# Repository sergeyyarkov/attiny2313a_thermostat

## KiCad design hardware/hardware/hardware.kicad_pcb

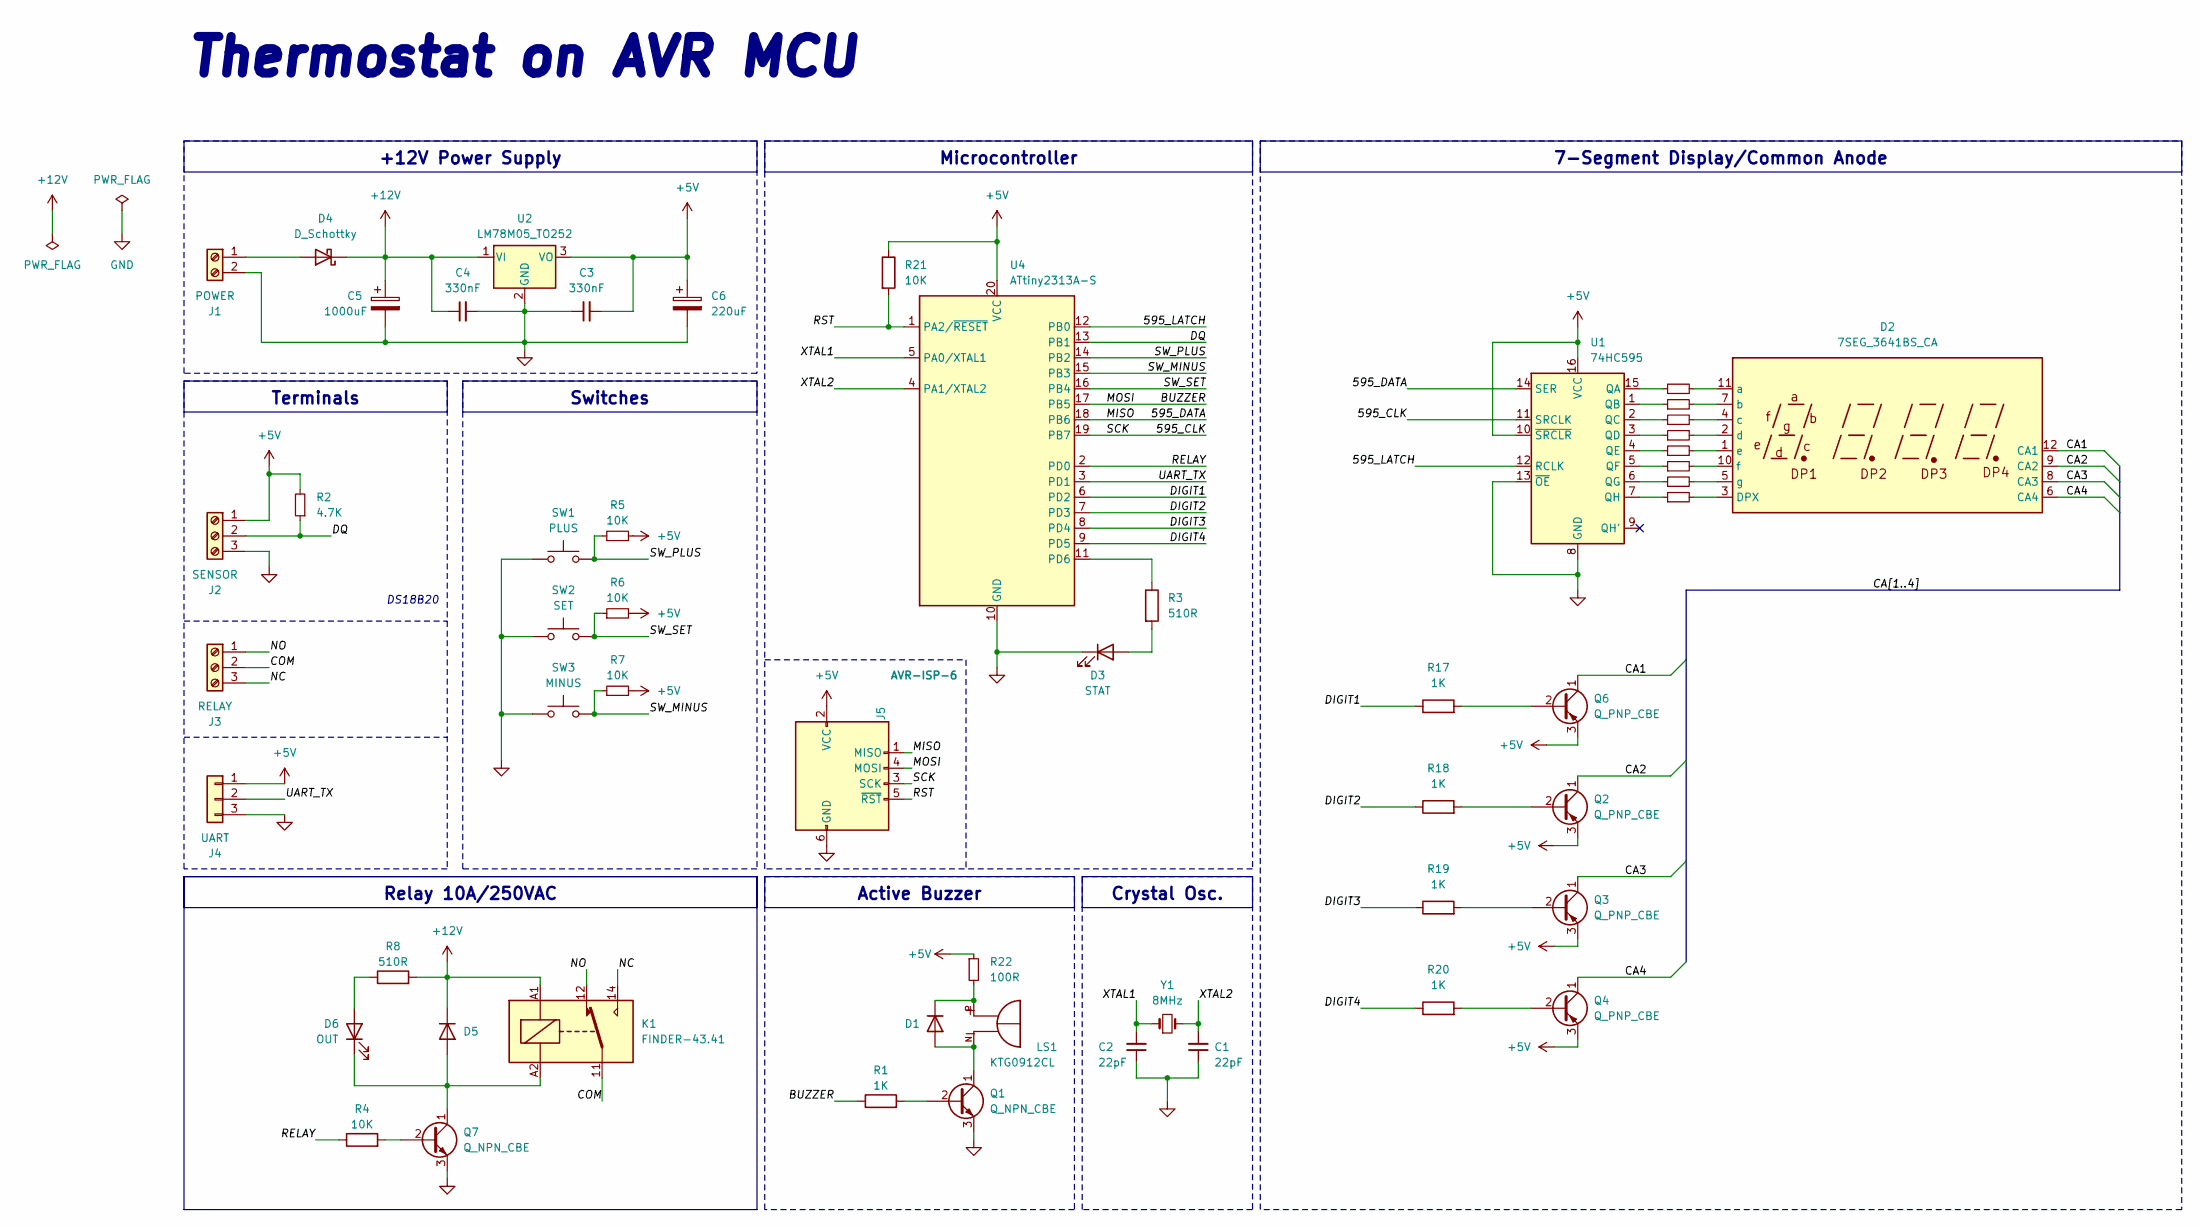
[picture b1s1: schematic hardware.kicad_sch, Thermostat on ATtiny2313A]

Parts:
C1, C2: 22pF; C_0805_2012Metric
C3, C4: 330nF; C_0805_2012Metric
C5: 1000uF; CP_Elec_10x10.5
C6: 220uF; CP_Elec_6.3x7.7
D1: 1N4448W; D_SOD-123
D2: 7SEG_3641BS_CA; 7SEG_3641BS
D3: STAT; LED_0805_2012Metric
D4: D_Schottky; D_SMA
D5: D; D_SMA
D6: OUT; LED_0805_2012Metric
J1: POWER; TerminalBlock_Phoenix_MPT-0,5-2-2.54_1x02_P2.54mm_Horizontal
J2: SENSOR; TerminalBlock_Phoenix_MPT-0,5-3-2.54_1x03_P2.54mm_Horizontal
J3: RELAY; TerminalBlock_Phoenix_MPT-0,5-3-2.54_1x03_P2.54mm_Horizontal
J4: UART; PinHeader_1x03_P2.54mm_Vertical
J5: AVR-ISP-6; PinHeader_2x03_P2.54mm_Vertical
K1: FINDER-43.41; RELAY_FINDER-43.41
LS1: KTG0912CL; XDCR_KTG0912CL; PARTREV 1.1
Q1, Q7: Q_NPN_CBE; SOT-23
Q2, Q3, Q4, Q6: Q_PNP_CBE; SOT-23
R1, R17, R18, R19, R20: 1K; R_0805_2012Metric
R2: 4.7K; R_0805_2012Metric
R3, R8: 510R; R_0805_2012Metric
R4, R5, R6, R7, R21: 10K; R_0805_2012Metric
R9, R10, R11, R12, R13, R14, R15, R16: 330R; R_0805_2012Metric
R22: 100R; R_0805_2012Metric
SW1: PLUS; SW_Push_1P1T_NO_6x6mm_H9.5mm
SW2: SET; SW_Push_1P1T_NO_6x6mm_H9.5mm
SW3: MINUS; SW_Push_1P1T_NO_6x6mm_H9.5mm
U1: 74HC595; SOIC-16W_5.3x10.2mm_P1.27mm
U2: LM78M05_TO252; TO-252-2
U4: ATtiny2313A-S; SOIC-20W_7.5x12.8mm_P1.27mm
Y1: 8MHz; Crystal_HC49-4H_Vertical

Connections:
+5V: C3.2, C6.1, J2.1, J4.1, J5.2 (VCC), Q2.3 (E), Q3.3 (E), Q4.3 (E), Q6.3 (E), R2.2, R5.2, R6.2, R7.2, R21.1, R22.1, U1.10 (~SRCLR), U1.16 (VCC), U2.3 (VO), U4.20 (VCC)
+12V: C4.1, C5.1, D4.1 (K), D5.1 (K), K1.A1, R8.2, U2.1 (VI)
/595_CLK: J5.3 (SCK), U1.11 (SRCLK), U4.19 (PB7)
/595_DATA: J5.1 (MISO), U1.14 (SER), U4.18 (PB6)
/595_LATCH: U1.12 (RCLK), U4.12 (PB0)
/BUZZER: J5.4 (MOSI), R1.1, U4.17 (PB5)
/CA1: D2.12 (CA1), Q6.1 (C)
/CA2: D2.9 (CA2), Q2.1 (C)
/CA3: D2.8 (CA3), Q3.1 (C)
/CA4: D2.6 (CA4), Q4.1 (C)
/COM: J3.2, K1.11
/DIGIT1: R17.1, U4.6 (PD2)
/DIGIT2: R18.1, U4.7 (PD3)
/DIGIT3: R19.1, U4.8 (PD4)
/DIGIT4: R20.1, U4.9 (PD5)
/DQ: J2.2, R2.1, U4.13 (PB1)
/NC: J3.3, K1.14
/NO: J3.1, K1.12
/RELAY: R4.1, U4.2 (PD0)
/RST: J5.5 (~RST), R21.2, U4.1 (PA2/~RESET)
/SW_MINUS: R7.1, SW3.2, U4.15 (PB3)
/SW_PLUS: R5.1, SW1.2, U4.14 (PB2)
/SW_SET: R6.1, SW2.2, U4.16 (PB4)
/UART_TX: J4.2, U4.3 (PD1)
/XTAL1: C2.2, U4.5 (PA0/XTAL1), Y1.1
/XTAL2: C1.2, U4.4 (PA1/XTAL2), Y1.2
GND: C1.1, C2.1, C3.1, C4.2, C5.2, C6.2, D3.1 (K), J1.2, J2.3, J4.3, J5.6 (GND), Q1.3 (E), Q7.3 (E), SW1.1, SW2.1, SW3.1, U1.8 (GND), U1.13 (~OE), U2.2 (GND), U4.10 (GND)
unnamed: D1.2 (A), LS1.N, Q1.1 (C)
unnamed: D1.1 (K), LS1.P, R22.2
unnamed: D2.3 (DPX), R16.2
unnamed: D2.11 (a), R9.2
unnamed: D2.7 (b), R10.2
unnamed: D2.4 (c), R11.2
unnamed: D2.2 (d), R12.2
unnamed: D2.1 (e), R13.2
unnamed: D2.10 (f), R14.2
unnamed: D2.5 (g), R15.2
unnamed: D3.2 (A), R3.2
unnamed: D4.2 (A), J1.1
unnamed: D5.2 (A), D6.1 (K), K1.A2, Q7.1 (C)
unnamed: D6.2 (A), R8.1
unnamed: Q1.2 (B), R1.2
unnamed: Q2.2 (B), R18.2
unnamed: Q3.2 (B), R19.2
unnamed: Q4.2 (B), R20.2
unnamed: Q6.2 (B), R17.2
unnamed: Q7.2 (B), R4.2
unnamed: R9.1, U1.15 (QA)
unnamed: R10.1, U1.1 (QB)
unnamed: R11.1, U1.2 (QC)
unnamed: R12.1, U1.3 (QD)
unnamed: R13.1, U1.4 (QE)
unnamed: R14.1, U1.5 (QF)
unnamed: R15.1, U1.6 (QG)
unnamed: R16.1, U1.7 (QH)
unnamed: R3.1, U4.11 (PD6)

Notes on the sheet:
Active Buzzer
Terminals
+12V Power Supply
Crystal Osc.
Relay 10A/250VAC
Switches
7-Segment Display/Common Anode
Microcontroller
Thermostat on AVR MCU
DS18B20

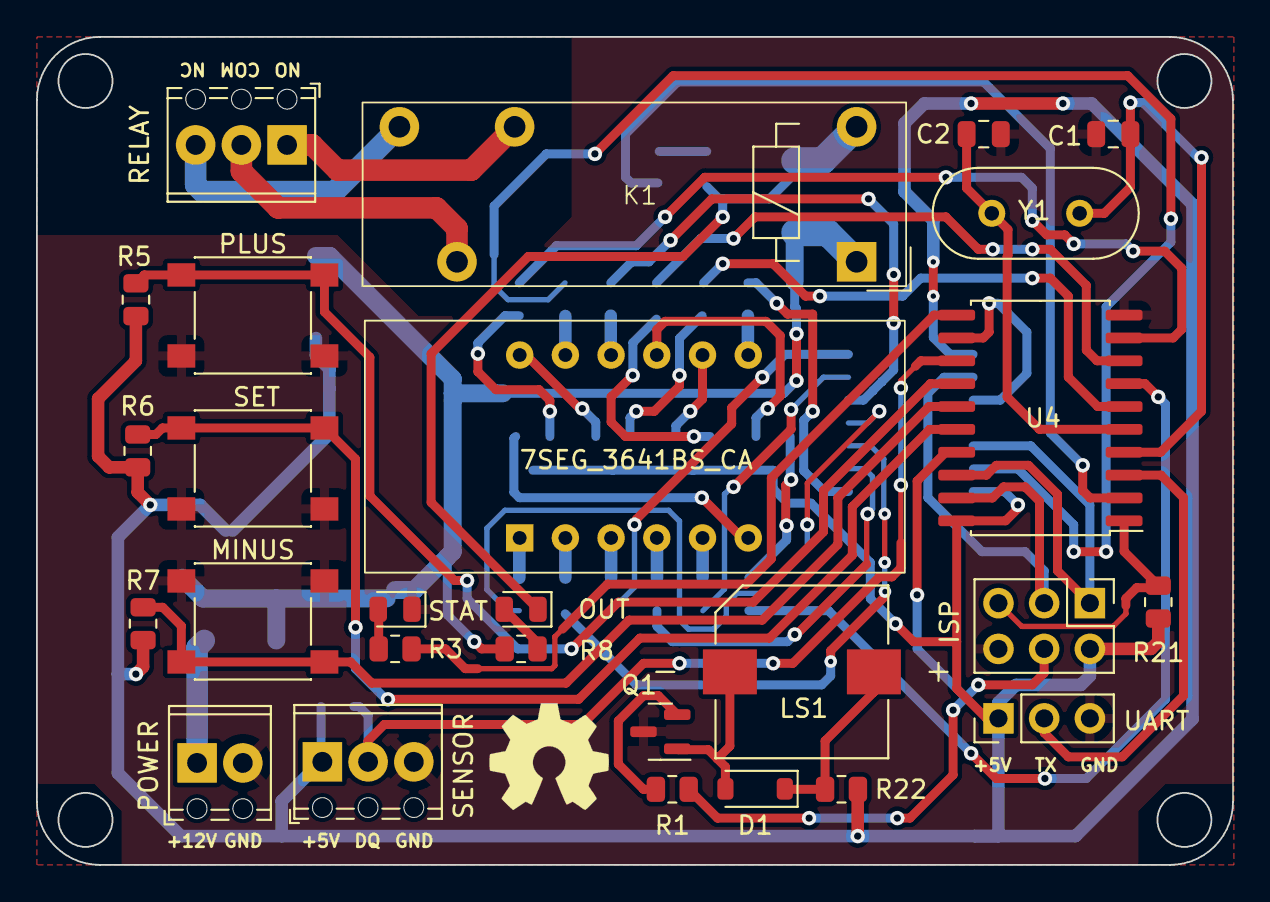
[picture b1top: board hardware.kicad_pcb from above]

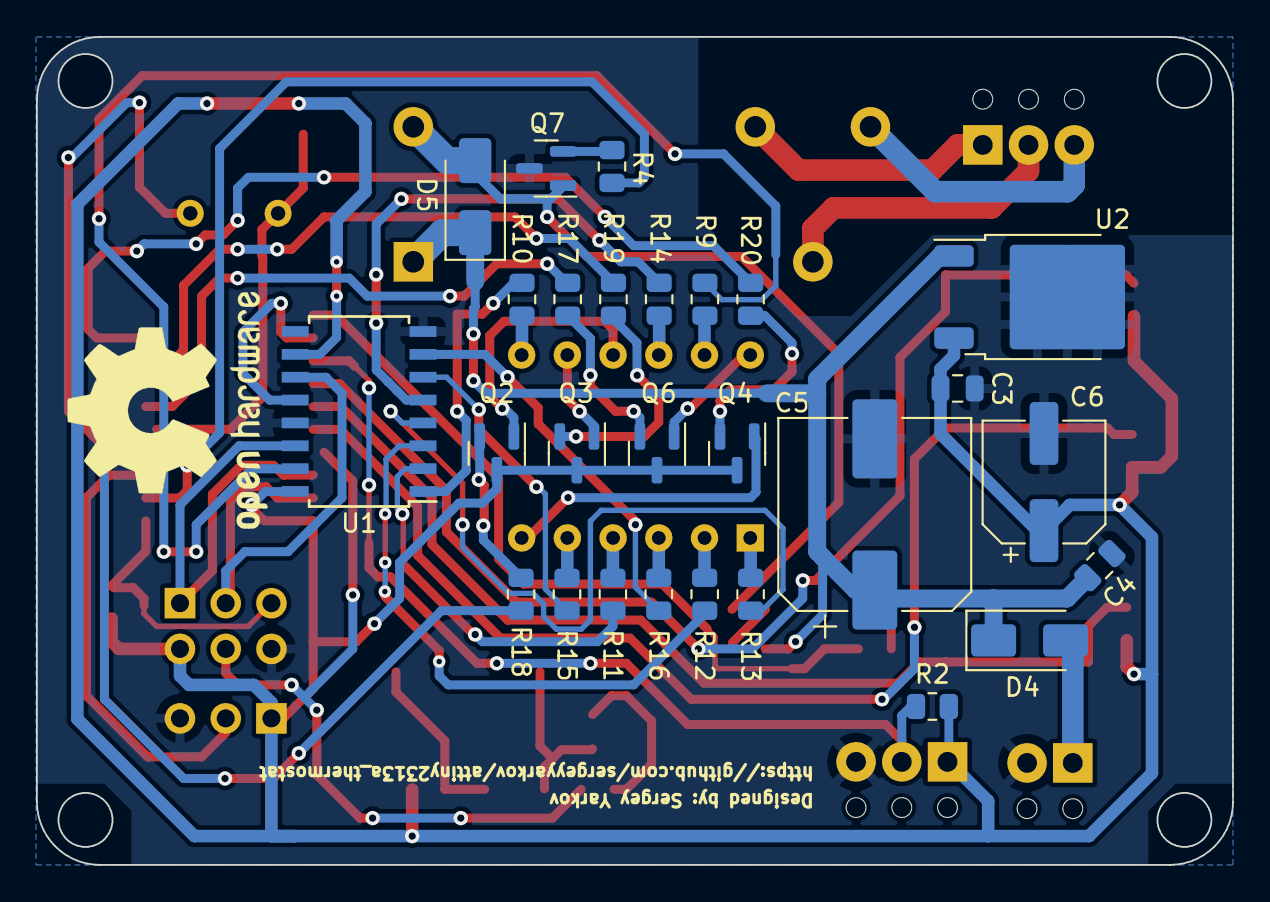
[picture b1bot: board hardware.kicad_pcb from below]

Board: 2 copper layers, 66.5 x 46.0 mm, 54 parts (27 on the bottom side), 56 nets.

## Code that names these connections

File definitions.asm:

.EQU F_CPU			= 8		; 8 Mhz (для задержки)   
 
.DEF TEMP_REG_A                 = r16
.DEF TEMP_REG_B                 = r17
.DEF DELAY_16_r			= r19
.DEF DELAY_8_r			= r20
.DEF DELAY_24_r			= r21
.DEF DISP_NUM_L                 = r24		; LSB числа которое сейчас на индикаторе
.DEF DISP_NUM_H                 = r25		; MSB числа которое сейчас на индикаторе
.DEF EEP_A_r			= r3
.DEF EEP_D_r			= r4
.DEF REPROGRAM_STEP_r		= r6

.EQU DIGIT_1_PIN                = PD2		; Пин разряда индикатора 1
.EQU DIGIT_2_PIN                = PD3		; Пин разряда индикатора 2
.EQU DIGIT_3_PIN                = PD4		; Пин разряда индикатора 3
.EQU DIGIT_4_PIN                = PD5		; Пин разряда индикатора 4

.EQU LED_PGM_PIN		= PD6		; Светодиод который говорит о том, что МК в состоянии настройки 
.EQU LED_PGM_PORT		= PORTD
    
.EQU OW_LINE			= PB1		; Пин шины 1-Wire
.EQU OW_DDR			= DDRB
.EQU OW_PIN			= PINB
.DEF OW_CMD_r			= r8
.DEF OWFR			= r23		; Флаги состояния для 1-Wire интерфейса
.EQU OWPRF                      = 0		; 1-Wire Флаг присутствия
.EQU OWSB                       = 1		; Флаг передачи одного бита

; **** КОМАНДЫ ДАТЧИКА *****************************************
.EQU DS18B20_CMD_CONVERTTEMP    = 0x44
.EQU DS18B20_CMD_RSCRATCHPAD    = 0xbe
.EQU DS18B20_CMD_WSCRATCHPAD    = 0x4e
.EQU DS18B20_CMD_CPYSCRATCHPAD  = 0x48
.EQU DS18B20_CMD_RECEEPROM      = 0xb8
.EQU DS18B20_CMD_RPWRSUPPLY     = 0xb4
.EQU DS18B20_CMD_SEARCHROM      = 0xf0
.EQU DS18B20_CMD_READROM        = 0x33
.EQU DS18B20_CMD_MATCHROM       = 0x55
.EQU DS18B20_CMD_SKIPROM        = 0xcc
.EQU DS18B20_CMD_ALARMSEARCH    = 0xec

.EQU USI_LATCH_PIN              = PB0		; ST_CP на 74HC595
.EQU USI_DO_PIN                 = PB6		; DS на 74HC595
.EQU USI_CLK_PIN                = PB7		; SH_CP на 74HC595

.EQU SW_PORT                    = PORTB
.EQU SW_PIN                     = PINB
.EQU SW_PLUS_PIN                = PB2		; Кнопка "Минус"
.EQU SW_MINUS_PIN               = PB3		; Кнопка "Плюс"
.EQU SW_SET_PIN                 = PB4		; Кнопка "Установить"
    
.EQU BUZZER_PIN			= PB5		; Пищалка
.EQU BUZZER_PORT		= PORTB
 
.EQU RELAY_PIN			= PD0		; Реле
.EQU RELAY_PORT			= PORTD
    
.EQU UART_TX_PIN		= PD1
    

.EQU MCU_STATE_DEFAULT          = 0x00		; Режим измерения температуры и сравнения с заданными параметрами
.EQU MCU_STATE_PROGRAM          = 0x01		; Режим настройки параметров в EEPROM
.EQU MCU_STATE_ERROR            = 0x02		; Режим ошибки, например когда не подключен датчик
    
.EQU MIN_HYST			= 1		; минимальный гистерезис который можно выставить - 0.1
.EQU MAX_HYST			= 200		; максимальный гистерезис который можно выставить - 20
    
.EQU MIN_TEMP_H			= 0xfe
.EQU MIN_TEMP_L			= 0x0c		; минимум -50 градусов уставка
.EQU MAX_TEMP_H			= 0x04		; максимум 120 градусов уставка
.EQU MAX_TEMP_L			= 0xb0		
    
; **** СТАНДАРТНЫЕ ПАРАМЕТРЫ ***********************************

.EQU DEFAULT_TEMP		= 300			    ; 30 градусов
.EQU DEFAULT_HYST		= 5			    ; 0.5 градусов гистерезис
    
.EQU HEAT_MODE			= 1
.EQU COOLING_MODE		= 0
.EQU DEFAULT_MODE		= HEAT_MODE

    
.EQU DEFAULT_SETTING_TEMP_L	= LOW(DEFAULT_TEMP)	
.EQU DEFAULT_SETTING_TEMP_H	= HIGH(DEFAULT_TEMP)
.EQU DEFAULT_SETTING_HYST	= DEFAULT_HYST
.EQU DEFAULT_SETTING_MODE	= DEFAULT_MODE
    
.EQU EEP_SETTING_TEMP_H		= 0x00
.EQU EEP_SETTING_TEMP_L		= 0x01
.EQU EEP_SETTING_HYST		= 0x02
.EQU EEP_SETTING_MODE		= 0x03
.EQU EEP_FIRST_TIME_RUN		= 0x04

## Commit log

2023-01-22 init project
2023-01-23 some delay
2023-01-28 shift register
2023-01-29 74hc595 transmit
2023-01-30 refactor
2023-02-25 display digits
2023-04-19 dynamic indication
2023-04-23 pint setup
2023-04-29 presence step 1wire
2023-05-10 1 wire presence detect
2023-06-19 one wire impl
2023-06-19 dist
2023-06-19 read temperature
2023-06-20 support signed ints
2023-06-20 support signed and unsigned fractional part
2023-06-22 buzzer
2023-06-22 fix dynamic indication
2023-06-22 relay pin
2023-06-24 check sensor family code
2023-06-25 read family code from ROM
2023-06-25 temperature comparsion
2023-06-26 cooling & heating modes compare
2023-06-26 send data to uart
2023-06-29 change hyst & temp settings
2023-06-29 program mode setting
2023-06-29 changed set temperature step
2023-06-30 save setting to eeprom
2023-06-30 min & max limit for temp setting
2023-07-01 fixed dot
2023-07-01 date
2023-07-01 folder structure
2023-07-01 terminal view in web-browser
2023-07-01 add proteus project file
2023-07-02 create project
